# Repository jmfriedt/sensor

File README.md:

Source code for a wireless acoustic sensor short range RADAR reader I used to develop. 15 years of time wasted
on a useless application ... just in case someone can figure out how to make good use of it. Good luck.
If interested enough feel free to reach me, email address easily found on the internet, blueprint for PCBs and prototypes still available if interested.

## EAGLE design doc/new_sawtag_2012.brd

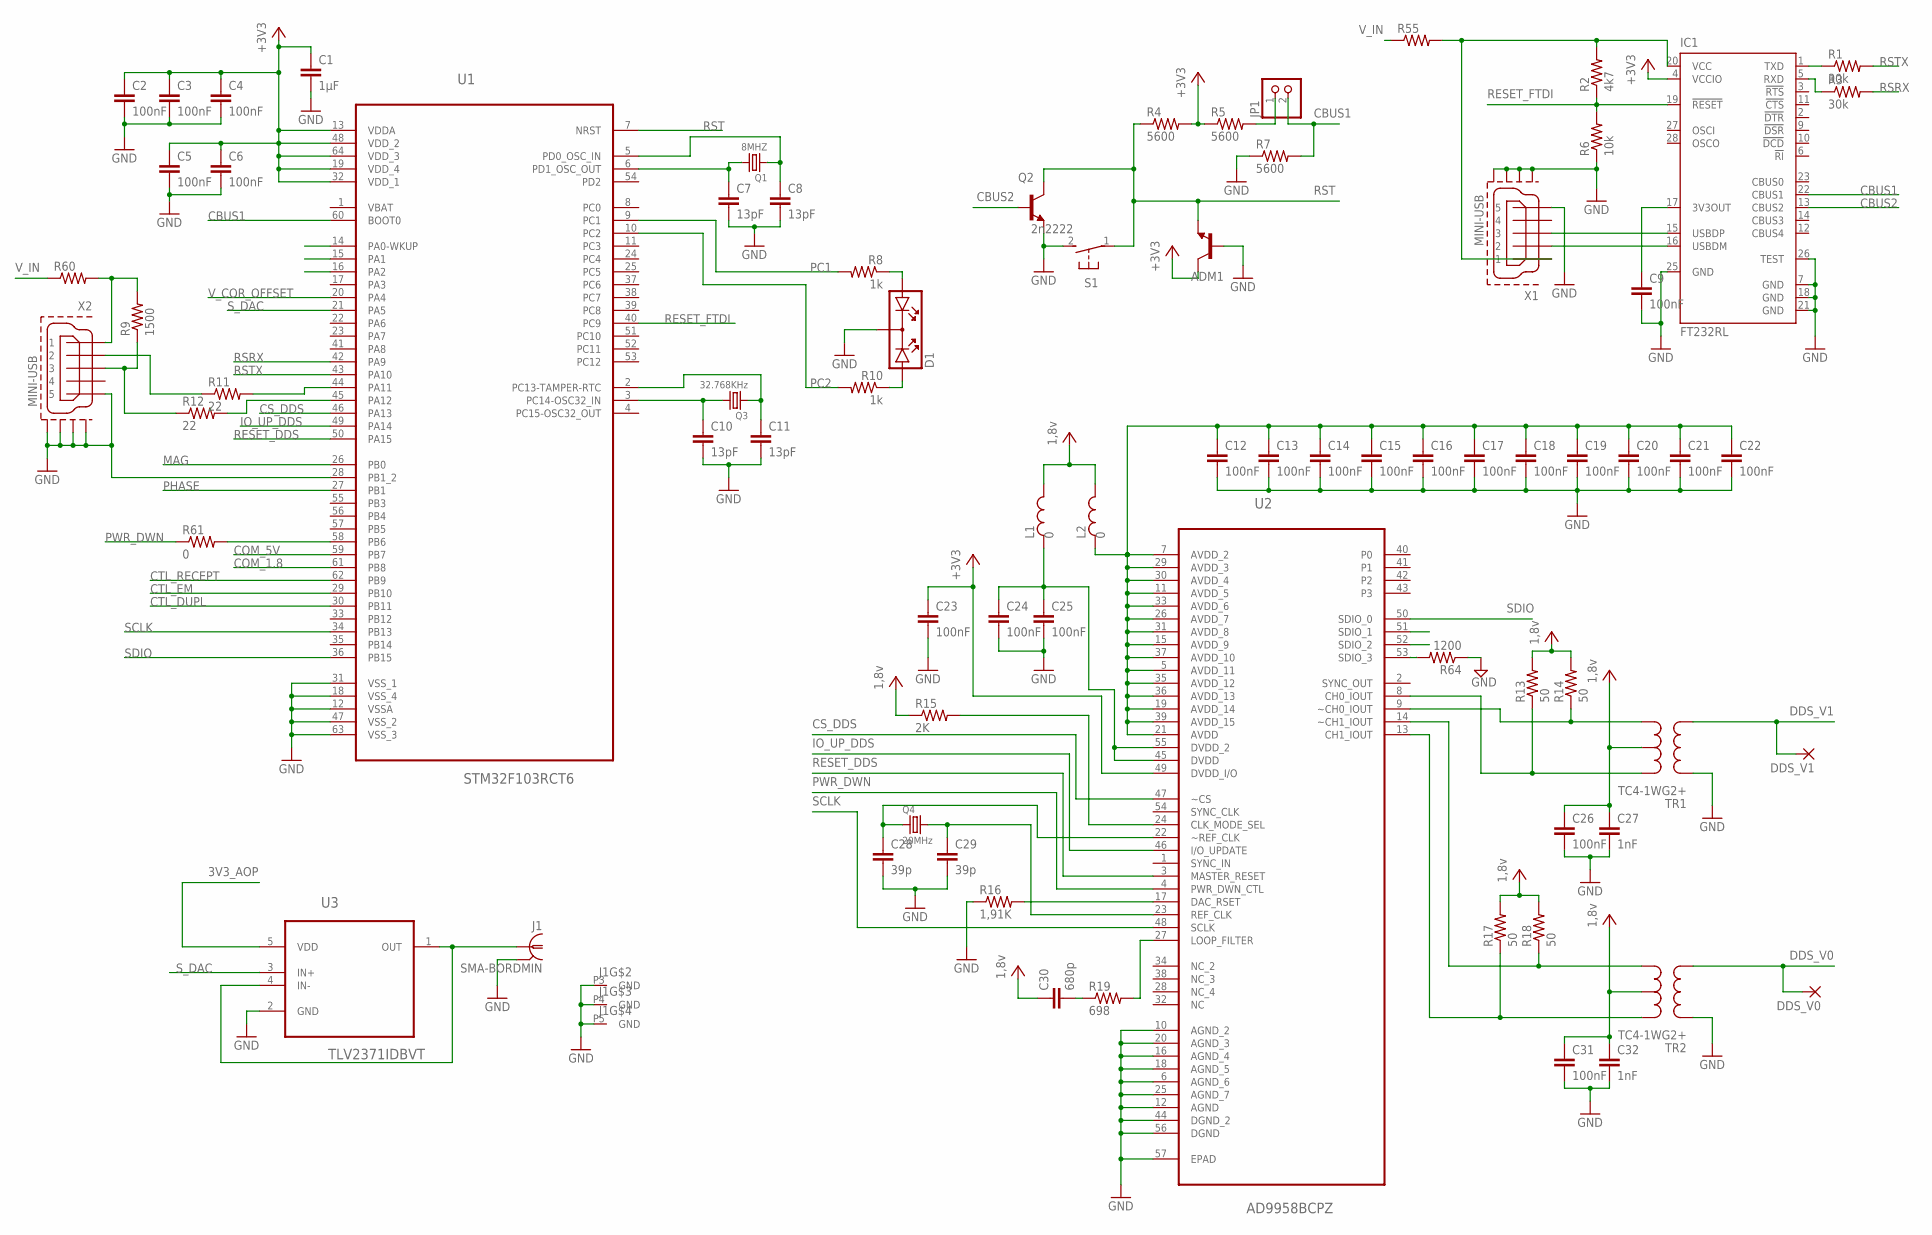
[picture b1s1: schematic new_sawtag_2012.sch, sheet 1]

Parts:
ADM1: TRANSISTOR_NPNSOT23; SOT23
C1: 1µF; C0805
C2, C3, C4, C5, C6, C9, C23, C24, C25, C26, C31: 100nF; C0603
C7, C8, C10, C11: 13pF; C0603
C12, C13, C14, C15, C16, C17, C18, C19, C20, C21, C22: 100nF; C0402
C27, C32: 1nF; C0402
C28, C29: 39p; C0402
C30: 680p; C0402
D1: DUOLED
DDS_V0, DDS_V1: 1,6/0,8
IC1: FT232RL; SSOP28
J1: SMA-BORDMIN; SMA_BORDMIN
JP1: PINHD-1X2; 1X02
L1, L2: 0; 0603
Q1: 8MHZ; SMD_5*3
Q2: 2n2222; SOT23
Q3: 32.768KHz; SMD_32K
Q4: 20MHz; SMD_5*3
R1, R3: 30k; R0402
R2: 4k7; R0402
R4, R5, R7: 5600; R0603
R6: 10k; R0402
R8, R10: 1k; R0603
R9: 1500; R1206
R11, R12: 22; R0603
R13, R14, R17, R18: 50; R0402
R15: 2K; R0402
R16: 1,91K; R0402
R19: 698; R0402
R55, R60: R-US_R2512; R2512
R61: 0; R0603
R64: 1200; R0402
S1: 31-XX; B3F-31XX
TR1, TR2: TC4-1WG2+; AT224-3
U1: STM32F103RCT6; QFP50P1200X1200X160-64N
U2: AD9958BCPZ; QFN50P800X800X100-57N
U3: TLV2371IDBVT; SOT95P280X145-5N
X1, X2: MINI-USB; UX60-MB-5ST

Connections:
3V3_AOP: U3.5 (VDD); also elsewhere on the board
+3V3: ADM1.3 (C), C1.1, C2.1, C3.1, C4.1, C5.1, C6.1, C23.1, IC1.4 (VCCIO), R4.2, R5.1, U1.13 (VDDA), U1.19 (VDD_4), U1.32 (VDD_1), U1.48 (VDD_2), U1.64 (VDD_3), U2.49 (DVDD_I/O); also elsewhere on the board
ALDDS: C12.1, C13.1, C14.1, C15.1, C16.1, C17.1, C18.1, C19.1, C20.1, C21.1, C22.1, L2.1, U2.5 (AVDD_11), U2.7 (AVDD_2), U2.11 (AVDD_5), U2.15 (AVDD_9), U2.19 (AVDD_14), U2.21 (AVDD), U2.26 (AVDD_7), U2.29 (AVDD_3), U2.30 (AVDD_4), U2.31 (AVDD_8), U2.33 (AVDD_6), U2.35 (AVDD_12), U2.36 (AVDD_13), U2.37 (AVDD_10), U2.39 (AVDD_15)
CBUS1: IC1.22 (CBUS1), JP1.2, R7.2, U1.60 (BOOT0)
CBUS2: IC1.13 (CBUS2), Q2.1 (B)
COM_1.8: U1.61 (PB8); also elsewhere on the board
COM_5V: U1.59 (PB7); also elsewhere on the board
CS_DDS: U1.46 (PA13), U2.47 (~CS)
CTL_DUPL: U1.30 (PB11); also elsewhere on the board
CTL_EM: U1.29 (PB10); also elsewhere on the board
CTL_RECEPT: U1.62 (PB9); also elsewhere on the board
DDS_V0: DDS_V0.1, TR2.P6 (P2); also elsewhere on the board
DDS_V1: DDS_V1.1, TR1.P6 (P2); also elsewhere on the board
GND: ADM1.1 (B), C1.2, C2.2, C3.2, C4.2, C5.2, C6.2, C7.2, C8.2, C9.2, C10.2, C11.2, C12.2, C13.2, C14.2, C15.2, C16.2, C17.2, C18.2, C19.2, C20.2, C21.2, C22.2, C23.2, C24.2, C25.2, C26.2, C27.2, C28.2, C29.2, C31.2, C32.2, D1.K, IC1.7 (GND), IC1.18 (GND), IC1.21 (GND), IC1.25 (GND), IC1.26 (TEST), J1.P1 (GND), J1.P3 (GND), J1.P4 (GND), J1.P5 (GND), Q2.2 (E), R6.1, R7.1, R16.1, R64.1, S1.2 (S), TR1.P4 (P1), TR2.P4 (P1), U1.12 (VSSA), U1.18 (VSS_4), U1.28 (PB1_2), U1.31 (VSS_1), U1.47 (VSS_2), U1.63 (VSS_3), U2.6 (AGND_6), U2.10 (AGND_2), U2.12 (AGND), U2.16 (AGND_4), U2.18 (AGND_5), U2.20 (AGND_3), U2.25 (AGND_7), U2.44 (DGND_2), U2.56 (DGND), U2.57 (EPAD), U3.2 (GND), X1.5, X1.M1 (GND1), X1.M2 (GND2), X1.M3 (GND3), X1.M4 (GND4), X2.5, X2.M1 (GND1), X2.M2 (GND2), X2.M3 (GND3), X2.M4 (GND4); also elsewhere on the board
IO_UP_DDS: U1.49 (PA14), U2.46 (I/O_UPDATE)
MAG: U1.26 (PB0); also elsewhere on the board
unnamed: R16.2, U2.17 (DAC_RSET)
unnamed: R19.2, U2.27 (LOOP_FILTER)
unnamed: C30.2, R19.1
unnamed: C28.1, Q4.P$1 (1), U2.22 (~REF_CLK)
unnamed: C29.1, Q4.P$3 (2), U2.23 (REF_CLK)
unnamed: R15.2, U2.24 (CLK_MODE_SEL)
unnamed: R17.1, TR2.P3 (S1), U2.13 (CH1_IOUT)
unnamed: R18.1, TR2.P1 (S3), U2.14 (~CH1_IOUT)
unnamed: R14.1, TR1.P1 (S3), U2.9 (~CH0_IOUT)
unnamed: R13.1, TR1.P3 (S1), U2.8 (CH0_IOUT)
unnamed: C24.1, C25.1, L1.1, U2.45 (DVDD), U2.55 (DVDD_2)
unnamed: R9.2, R60.2, X2.1
unnamed: J1.P2 (1), U3.1 (OUT), U3.4 (IN-)
unnamed: R61.2, U1.58 (PB6)
unnamed: R11.2, U1.44 (PA11)
unnamed: IC1.16 (USBDM), X1.2
unnamed: IC1.20 (VCC), R2.2, R55.2, X1.1
unnamed: R12.2, U1.45 (PA12)
unnamed: IC1.15 (USBDP), X1.3
unnamed: C9.1, IC1.17 (3V3OUT)
unnamed: IC1.1 (TXD), R1.1
unnamed: IC1.5 (RXD), R3.1
unnamed: C8.1, Q1.P$1 (1), U1.5 (PD0_OSC_IN)
unnamed: JP1.1, R5.2
unnamed: C7.1, Q1.P$3 (2), U1.6 (PD1_OSC_OUT)
unnamed: R11.1, X2.2
unnamed: D1.A2, R8.1
unnamed: C10.1, Q3.P$2 (2), U1.3 (PC14-OSC32_IN)
unnamed: C11.1, Q3.P$1 (1), U1.2 (PC13-TAMPER-RTC)
unnamed: D1.A1, R10.1
unnamed: R9.1, R12.1, X2.3
PA7: U1.23 (PA7)
PC1: R8.2, U1.9 (PC1)
PC2: R10.2, U1.10 (PC2)
PHASE: U1.27 (PB1); also elsewhere on the board
PWR_DWN: R61.1, U2.4 (PWR_DWN_CTL)
RESET_DDS: U1.50 (PA15), U2.3 (MASTER_RESET)
RESET_FTDI: IC1.19 (!RESET), R2.1, R6.2, U1.40 (PC9)
RSRX: R3.2, U1.42 (PA9)
RST: ADM1.2 (E), Q2.3 (C), R4.1, S1.1, U1.7 (NRST)
RSTX: R1.2, U1.43 (PA10)
SCLK: U1.34 (PB13), U2.48 (SCLK)
SDIO: U1.36 (PB15), U2.50 (SDIO_0)
SDIO_1: U1.14 (PA0-WKUP), U2.51 (SDIO_1)
SDIO_2: U1.15 (PA1), U2.52 (SDIO_2)
SDIO_3: R64.2, U1.16 (PA2), U2.53 (SDIO_3)
S_DAC: U1.21 (PA5), U3.3 (IN+)
VCC: C26.1, C27.1, C30.1, C31.1, C32.1, L1.2, L2.2, R13.2, R14.2, R15.1, R17.2, R18.2, TR1.P2 (S2), TR2.P2 (S2); also elsewhere on the board
V_COR_OFFSET: U1.20 (PA4); also elsewhere on the board
V_IN: R55.1, R60.1; also elsewhere on the board

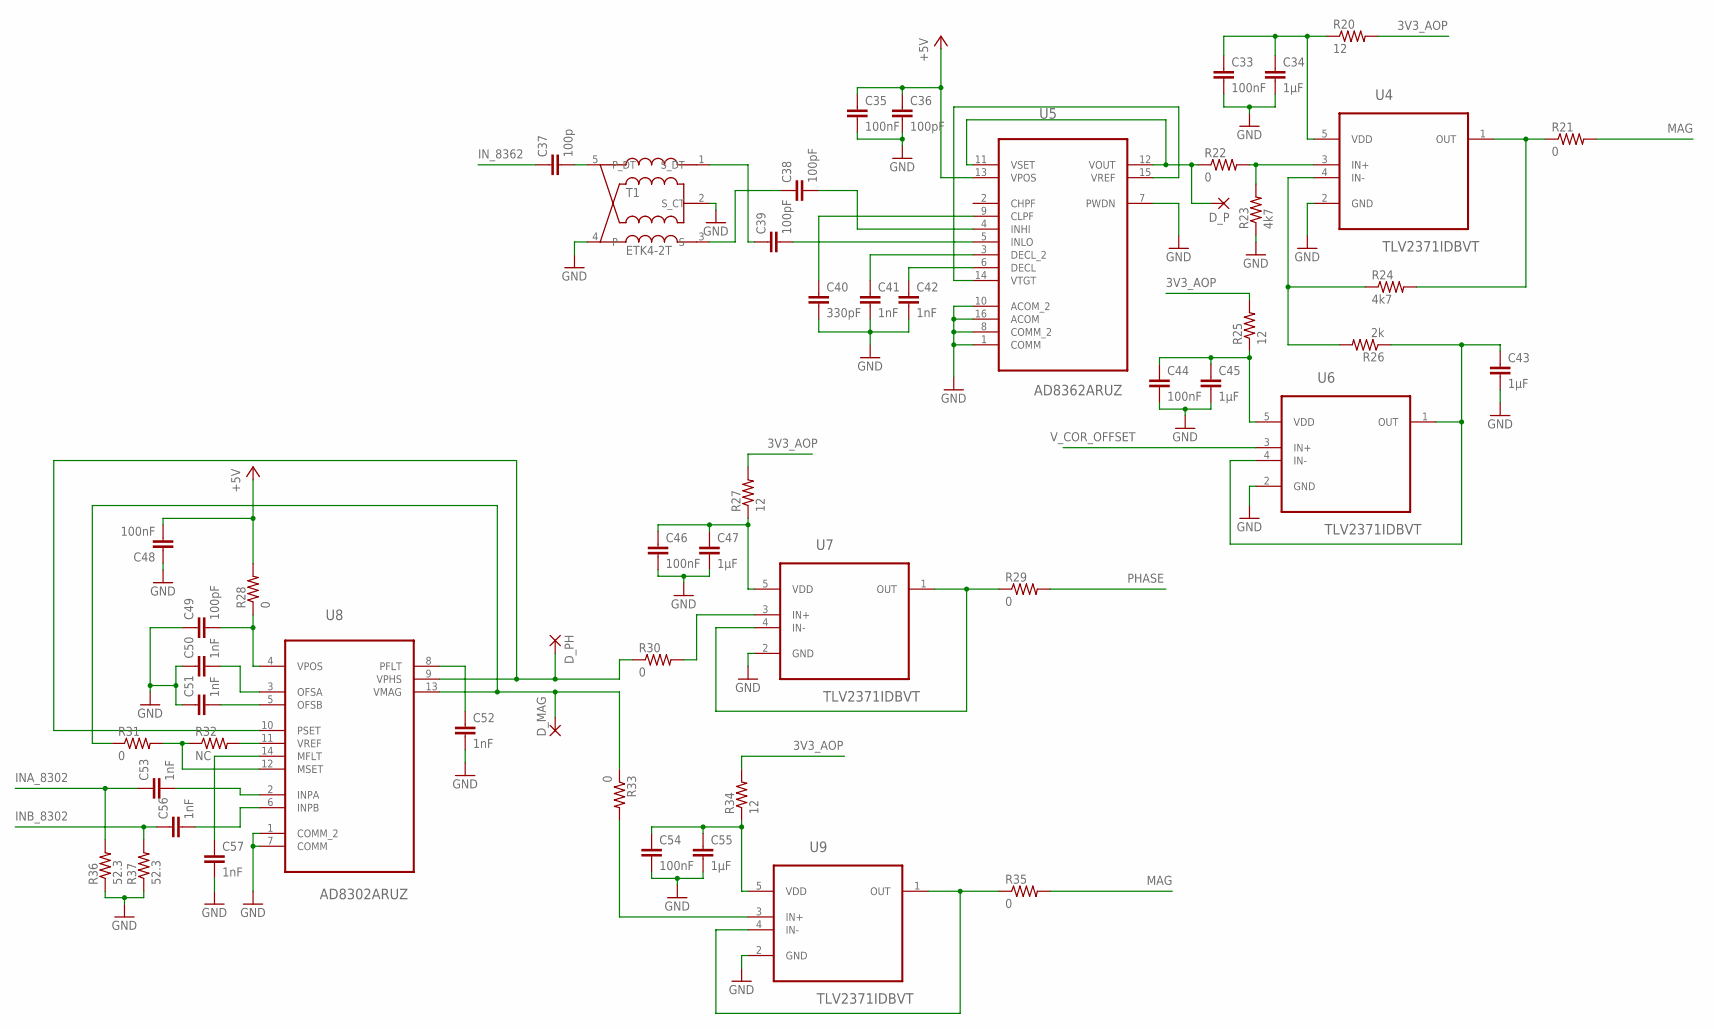
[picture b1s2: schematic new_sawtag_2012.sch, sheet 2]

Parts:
C33, C44, C46, C54: 100nF; C0402
C34, C43, C45, C47, C55: 1µF; C0603
C35, C48: 100nF; C0603
C36: 100pF; C0603
C37: 100p; C0402
C38, C39, C49: 100pF; C0402
C40: 330pF; C0603
C41, C42: 1nF; C0603
C50, C51, C52, C53, C56, C57: 1nF; C0402
D_MAG: 1,6/0,8
D_P: 1,6/0,8
D_PH: 1,6/0,8
R20, R25, R27, R34: 12; R0603
R21, R22, R28, R29, R30, R31, R33, R35: 0; R0603
R23, R24: 4k7; R0603
R26: 2k; R0603
R32: NC; R0603
R36, R37: 52.3; R0603
T1: ETK4-2T; SM-22
U4: TLV2371IDBVT; SOT95P280X145-5N
U5: AD8362ARUZ; SOP65P640X120-16N
U6, U7, U9: TLV2371IDBVT; SOT95P280X145-5N; MPN TLV2371IDBVT
U8: AD8302ARUZ; SOP65P640X120-14N

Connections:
3V3_AOP: R20.2, R25.2, R27.2, R34.2; also elsewhere on the board
+5V: C35.1, C36.1, C48.2, R28.2, U5.13 (VPOS); also elsewhere on the board
GND: C33.2, C34.2, C35.2, C36.2, C40.2, C41.2, C42.2, C43.2, C44.2, C45.2, C46.2, C47.2, C48.1, C49.1, C50.1, C51.1, C52.2, C54.2, C55.2, C57.2, R23.1, R36.1, R37.1, T1.2 (S_CT), T1.4, U4.2 (GND), U5.1 (COMM), U5.7 (PWDN), U5.8 (COMM_2), U5.10 (ACOM_2), U5.16 (ACOM), U6.2 (GND), U7.2 (GND), U8.1 (COMM_2), U8.7 (COMM), U9.2 (GND); also elsewhere on the board
INA_8302: C53.1, R36.2; also elsewhere on the board
INB_8302: C56.1, R37.2; also elsewhere on the board
IN_8362: C37.1; also elsewhere on the board
MAG: R21.2, R35.2; also elsewhere on the board
unnamed: D_P.1, R22.1, U5.11 (VSET), U5.12 (VOUT)
unnamed: R22.2, R23.2, U4.3 (IN+)
unnamed: C42.1, U5.6 (DECL)
unnamed: C41.1, U5.3 (DECL_2)
unnamed: C40.1, U5.9 (CLPF)
unnamed: C39.2, U5.5 (INLO)
unnamed: C38.2, U5.4 (INHI)
unnamed: R24.1, R26.2, U4.4 (IN-)
unnamed: U5.14 (VTGT), U5.15 (VREF)
unnamed: C43.1, R26.1, U6.1 (OUT), U6.4 (IN-)
unnamed: C33.1, C34.1, R20.1, U4.5 (VDD)
unnamed: C50.2, U8.3 (OFSA)
unnamed: C51.2, U8.5 (OFSB)
unnamed: C53.2, U8.2 (INPA)
unnamed: C56.2, U8.6 (INPB)
unnamed: C44.1, C45.1, R25.1, U6.5 (VDD)
unnamed: C49.2, R28.1, U8.4 (VPOS)
unnamed: R30.2, U7.3 (IN+)
unnamed: R29.1, U7.1 (OUT), U7.4 (IN-)
unnamed: R33.2, U9.3 (IN+)
unnamed: R35.1, U9.1 (OUT), U9.4 (IN-)
unnamed: C46.1, C47.1, R27.1, U7.5 (VDD)
unnamed: C54.1, C55.1, R34.1, U9.5 (VDD)
unnamed: D_MAG.1, R31.1, R33.1, U8.13 (VMAG)
unnamed: D_PH.1, R30.1, U8.9 (VPHS), U8.10 (PSET)
unnamed: C39.1, T1.1 (S_DT)
unnamed: C38.1, T1.3 (S)
unnamed: C57.1, U8.14 (MFLT)
unnamed: C52.1, U8.8 (PFLT)
unnamed: C37.2, T1.5 (P_DT)
unnamed: R21.1, R24.2, U4.1 (OUT)
unnamed: R31.2, R32.1, U8.12 (MSET)
unnamed: R32.2, U8.11 (VREF)
PHASE: R29.2; also elsewhere on the board
V_COR_OFFSET: U6.3 (IN+); also elsewhere on the board

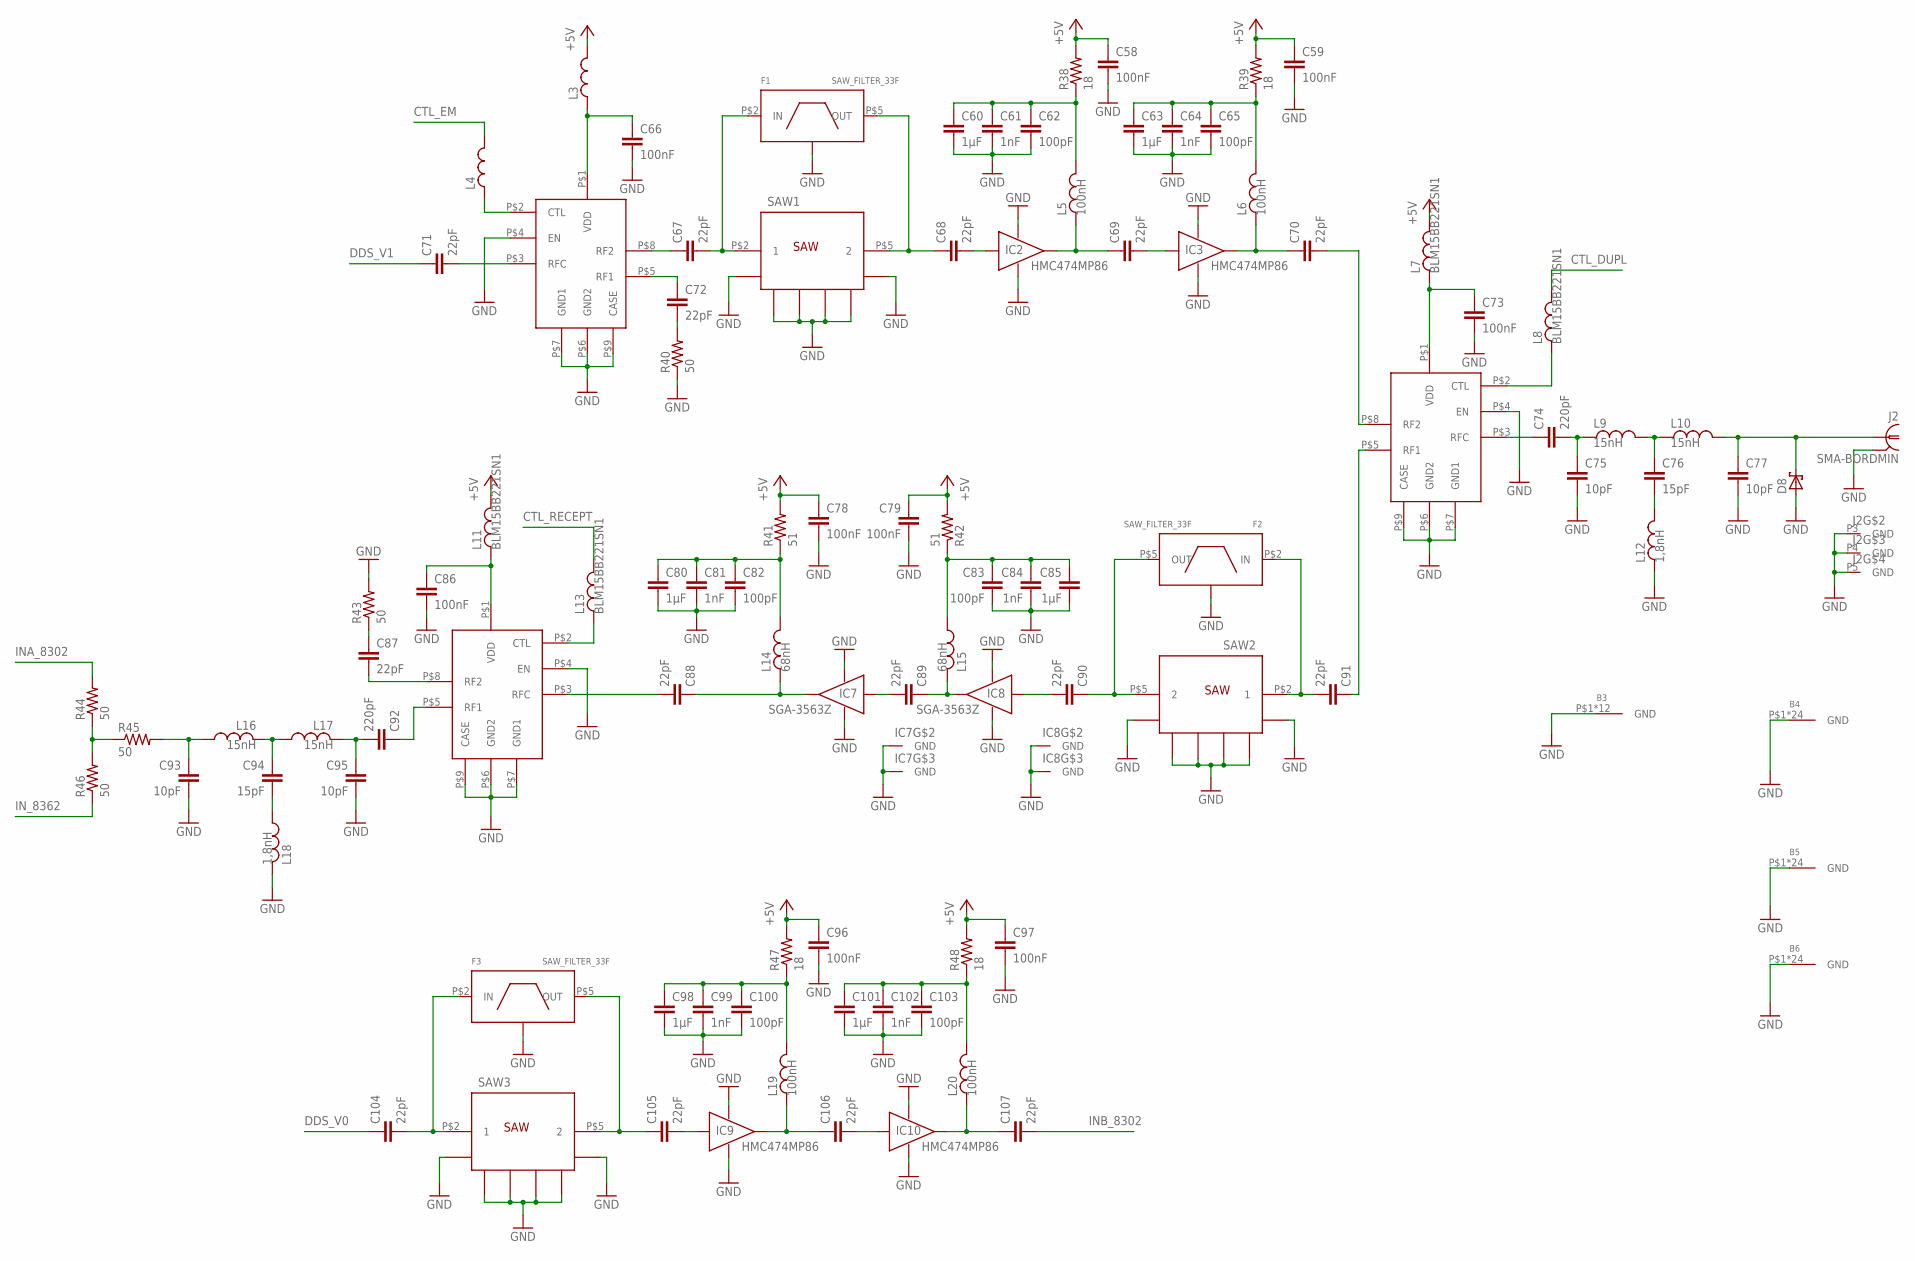
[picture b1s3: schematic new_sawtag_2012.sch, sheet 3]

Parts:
B3: BMIS-102
B4, B5, B6: BMIS-205
C58, C59, C66, C78, C79, C86, C96, C97: 100nF; C0603
C60, C63, C80, C85, C98, C101: 1µF; C0603
C61, C64, C81, C84, C99, C102: 1nF; C0402
C62, C65, C82, C83, C100, C103: 100pF; C0402
C67, C68, C69, C70, C71, C72, C87, C88, C89, C90, C91, C104, C105, C106, C107: 22pF; C0402
C73: 100nF; C0402
C74, C92: 220pF; C0402
C75, C77, C93, C95: 10pF; C0402
C76, C94: 15pF; C0402
D8: SMF5.0AT1; SOD123FL
F1, F2, F3: SAW_FILTER_33F; BOITIER_3-3
IC2, IC3, IC9, IC10: HMC474MP86; VV105
IC4, IC5, IC6: HMC349MS8G; SMT-MS8G
IC7, IC8: SGA-3563Z; SOT363
J2: SMA-BORDMIN; SMA_BORDMIN
L3, L4: L_0402; 0402
L5, L6, L19, L20: 100nH; 0603
L7, L8, L11, L13: BLM15BB221SN1; 0402
L9, L10, L16, L17: 15nH; 0603
L12, L18: 1,8nH; 0603
L14, L15: 68nH; 0603
R38, R39, R47, R48: 18; R0603
R40: 50; R0603
R41, R42: 51; R0603
R43, R44, R45, R46: 50; R0402
SAW1, SAW2, SAW3: SAW_DBLPORT; BOITIER_5-5

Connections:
+5V: C58.1, C59.1, C78.1, C79.1, C96.1, C97.1, L3.2, L7.2, L11.2, R38.2, R39.2, R41.2, R42.2, R47.2, R48.2; also elsewhere on the board
CTL_DUPL: L8.2; also elsewhere on the board
CTL_EM: L4.2; also elsewhere on the board
CTL_RECEPT: L13.2; also elsewhere on the board
DDS_V0: C104.1; also elsewhere on the board
DDS_V1: C71.1; also elsewhere on the board
GND: B3.P$1, B3.P$2, B3.P$3, B3.P$4, B3.P$5, B3.P$6, B3.P$7, B3.P$8, B3.P$9, B3.P$10, B3.P$11, B3.P$12, B4.P$1, B4.P$2, B4.P$3, B4.P$4, B4.P$5, B4.P$6, B4.P$7, B4.P$8, B4.P$9, B4.P$10, B4.P$11, B4.P$12, B4.P$13, B4.P$14, B4.P$15, B4.P$16, B4.P$17, B4.P$18, B4.P$19, B4.P$20, B4.P$21, B4.P$22, B4.P$23, B4.P$24, B5.P$1, B5.P$2, B5.P$3, B5.P$4, B5.P$5, B5.P$6, B5.P$7, B5.P$8, B5.P$9, B5.P$10, B5.P$11, B5.P$12, B5.P$13, B5.P$14, B5.P$15, B5.P$16, B5.P$17, B5.P$18, B5.P$19, B5.P$20, B5.P$21, B5.P$22, B5.P$23, B5.P$24, B6.P$1, B6.P$2, B6.P$3, B6.P$4, B6.P$5, B6.P$6, B6.P$7, B6.P$8, B6.P$9, B6.P$10, B6.P$11, B6.P$12, B6.P$13, B6.P$14, B6.P$15, B6.P$16, B6.P$17, B6.P$18, B6.P$19, B6.P$20, B6.P$21, B6.P$22, B6.P$23, B6.P$24, C58.2, C59.2, C60.2, C61.2, C62.2, C63.2, C64.2, C65.2, C66.2, C73.2, C75.2, C77.2, C78.2, C79.2, C80.2, C81.2, C82.2, C83.2, C84.2, C85.2, C86.2, C93.2, C95.2, C96.2, C97.2, C98.2, C99.2, C100.2, C101.2, C102.2, C103.2, D8.A, F1.P$1, F1.P$3 (GND), F1.P$4 (GND), F1.P$6 (GND), F2.P$1, F2.P$3 (GND), F2.P$4 (GND), F2.P$6 (GND), F3.P$1, F3.P$3 (GND), F3.P$4 (GND), F3.P$6 (GND), IC2.2 (V_1), IC2.4 (V_2), IC3.2 (V_1), IC3.4 (V_2), IC4.P$4 (EN), IC4.P$6 (GND2), IC4.P$7 (GND1), IC4.P$9 (CASE), IC5.P$4 (EN), IC5.P$6 (GND2), IC5.P$7 (GND1), IC5.P$9 (CASE), IC6.P$4 (EN), IC6.P$6 (GND2), IC6.P$7 (GND1), IC6.P$9 (CASE), IC7.P$1 (V_1), IC7.P$2 (GND), IC7.P$4 (V_2), IC7.P$5 (GND), IC8.P$1 (V_1), IC8.P$2 (GND), IC8.P$4 (V_2), IC8.P$5 (GND), IC9.2 (V_1), IC9.4 (V_2), IC10.2 (V_1), IC10.4 (V_2), J2.P1 (GND), J2.P3 (GND), J2.P4 (GND), J2.P5 (GND), L12.1, L18.1, R40.1, R43.2, SAW1.P$1 (GND1), SAW1.P$3 (GND2), SAW1.P$4 (GND3), SAW1.P$6 (GND4), SAW1.P$7 (GND5), SAW1.P$8 (GND6), SAW2.P$1 (GND1), SAW2.P$3 (GND2), SAW2.P$4 (GND3), SAW2.P$6 (GND4), SAW2.P$7 (GND5), SAW2.P$8 (GND6), SAW3.P$1 (GND1), SAW3.P$3 (GND2), SAW3.P$4 (GND3), SAW3.P$6 (GND4), SAW3.P$7 (GND5), SAW3.P$8 (GND6); also elsewhere on the board
INA_8302: R44.2; also elsewhere on the board
INB_8302: C107.2; also elsewhere on the board
IN_8362: R46.1; also elsewhere on the board
unnamed: C67.2, F1.P$2 (IN), SAW1.P$2 (1)
unnamed: C67.1, IC4.P$8 (RF2)
unnamed: C70.1, IC3.3 (OUT), L6.1
unnamed: C68.1, F1.P$5 (OUT), SAW1.P$5 (2)
unnamed: C68.2, IC2.1 (IN)
unnamed: C63.1, C64.1, C65.1, L6.2, R39.1
unnamed: C72.1, IC4.P$5 (RF1)
unnamed: C60.1, C61.1, C62.1, L5.2, R38.1
unnamed: C69.1, IC2.3 (OUT), L5.1
unnamed: C69.2, IC3.1 (IN)
unnamed: C72.2, R40.2
unnamed: C91.2, F2.P$2 (IN), SAW2.P$2 (1)
unnamed: C91.1, IC5.P$5 (RF1)
unnamed: C90.1, F2.P$5 (OUT), SAW2.P$5 (2)
unnamed: C90.2, IC8.P$3 (IN)
unnamed: C89.1, IC8.P$6 (OUT), L15.1
unnamed: C83.1, C84.1, C85.1, L15.2, R42.1
unnamed: C88.1, IC7.P$6 (OUT), L14.1
unnamed: C80.1, C81.1, C82.1, L14.2, R41.1
unnamed: C89.2, IC7.P$3 (IN)
unnamed: C70.2, IC5.P$8 (RF2)
unnamed: C92.1, IC6.P$5 (RF1)
unnamed: C87.2, IC6.P$8 (RF2)
unnamed: C74.1, IC5.P$3 (RFC)
unnamed: C74.2, C75.1, L9.1
unnamed: C76.1, L9.2, L10.1
unnamed: C76.2, L12.2
unnamed: C77.1, D8.C, J2.P2 (1), L10.2
unnamed: C88.2, IC6.P$3 (RFC)
unnamed: C87.1, R43.1
unnamed: C73.1, IC5.P$1 (VDD), L7.1
unnamed: C92.2, C95.1, L17.1
unnamed: C94.1, L16.1, L17.2
unnamed: C94.2, L18.2
unnamed: C93.1, L16.2, R45.2
unnamed: IC5.P$2 (CTL), L8.1
unnamed: C66.1, IC4.P$1 (VDD), L3.1
unnamed: C71.2, IC4.P$3 (RFC)
unnamed: C86.1, IC6.P$1 (VDD), L11.1
unnamed: IC4.P$2 (CTL), L4.1
unnamed: IC6.P$2 (CTL), L13.1
unnamed: R44.1, R45.1, R46.2
unnamed: C104.2, F3.P$2 (IN), SAW3.P$2 (1)
unnamed: C105.1, F3.P$5 (OUT), SAW3.P$5 (2)
unnamed: C105.2, IC9.1 (IN)
unnamed: C98.1, C99.1, C100.1, L19.2, R47.1
unnamed: C106.1, IC9.3 (OUT), L19.1
unnamed: C106.2, IC10.1 (IN)
unnamed: C107.1, IC10.3 (OUT), L20.1
unnamed: C101.1, C102.1, C103.1, L20.2, R48.1

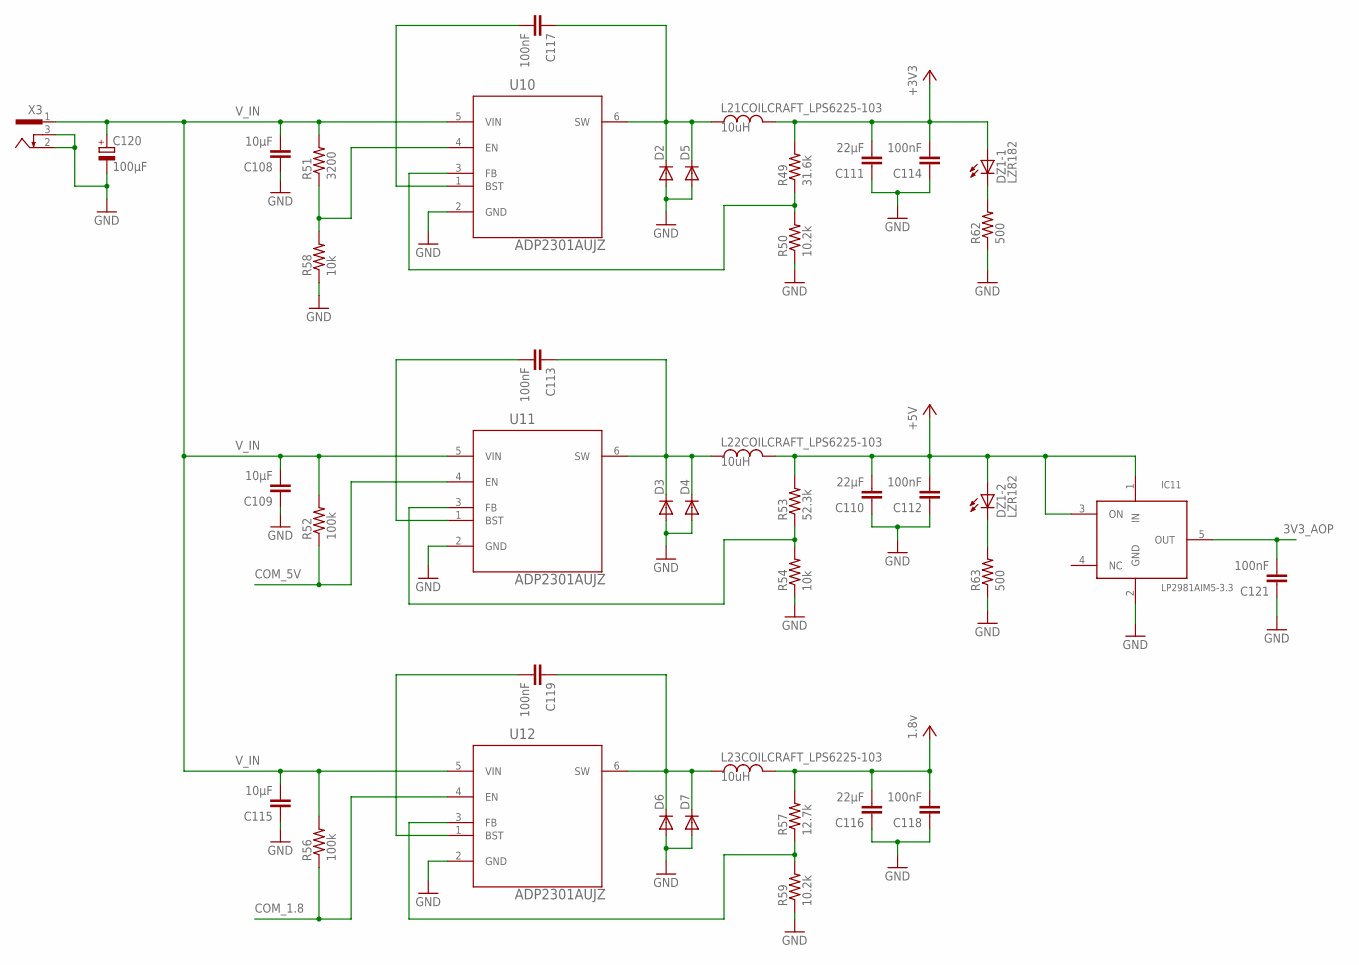
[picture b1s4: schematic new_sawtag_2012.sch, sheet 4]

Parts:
C108, C109, C115: 10µF; C0805
C110, C111, C116: 22µF; C0805
C112, C113, C114, C117, C118, C121: 100nF; C0805
C119: 100nF; C0603
C120: 100µF; 140CLH-1010
D2, D3, D6: DIODE-SMB; SMB
D4, D5, D7: DIODE-SMC; SMC
DZ1: LZR182
IC11: LP2981AIM5-3.3; SOT23-M5
L21COILCRAFT_LPS6225-103, L22COILCRAFT_LPS6225-103, L23COILCRAFT_LPS6225-103: 10uH; L_DCDC_6*6
R49: 31.6k; R0603
R50, R59: 10.2k; R0603
R51: 3200; R0603
R52, R56: 100k; R0603
R53: 52.3k; R0603
R54, R58: 10k; R0603
R57: 12.7k; R0603
R62, R63: 500; R0402
U10, U11, U12: ADP2301AUJZ; SOT95P280X90-6N
X3: 733980-62

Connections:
3V3_AOP: C121.2, IC11.5 (OUT); also elsewhere on the board
+3V3: C111.2, C114.2, DZ1.A1 (A), L21COILCRAFT_LPS6225-103.P$2 (2), R49.2; also elsewhere on the board
+5V: C110.2, C112.2, DZ1.A2 (A), IC11.1 (IN), IC11.3 (ON), L22COILCRAFT_LPS6225-103.P$2 (2), R53.2; also elsewhere on the board
COM_1.8: R56.1, U12.4 (EN); also elsewhere on the board
COM_5V: R52.1, U11.4 (EN); also elsewhere on the board
GND: C108.1, C109.1, C110.1, C111.1, C112.1, C114.1, C115.1, C116.1, C118.1, C120.-, C121.1, D2.A, D3.A, D4.A, D5.A, D6.A, D7.A, IC11.2 (GND), R50.1, R54.1, R58.1, R59.1, R62.1, R63.1, U10.2 (GND), U11.2 (GND), U12.2 (GND), X3.2, X3.3; also elsewhere on the board
unnamed: C113.1, D3.C, D4.C, L22COILCRAFT_LPS6225-103.P$1 (1), U11.6 (SW)
unnamed: C117.1, D2.C, D5.C, L21COILCRAFT_LPS6225-103.P$1 (1), U10.6 (SW)
unnamed: R49.1, R50.2, U10.3 (FB)
unnamed: R53.1, R54.2, U11.3 (FB)
unnamed: C117.2, U10.1 (BST)
unnamed: DZ1.K1 (C), R62.2
unnamed: R51.1, R58.2, U10.4 (EN)
unnamed: C113.2, U11.1 (BST)
unnamed: C119.1, D6.C, D7.C, L23COILCRAFT_LPS6225-103.P$1 (1), U12.6 (SW)
unnamed: R57.1, R59.2, U12.3 (FB)
unnamed: C119.2, U12.1 (BST)
unnamed: DZ1.K2 (C), R63.2
VCC: C116.2, C118.2, L23COILCRAFT_LPS6225-103.P$2 (2), R57.2; also elsewhere on the board
V_IN: C108.2, C109.2, C115.2, C120.+, R51.2, R52.2, R56.2, U10.5 (VIN), U11.5 (VIN), U12.5 (VIN), X3.1; also elsewhere on the board

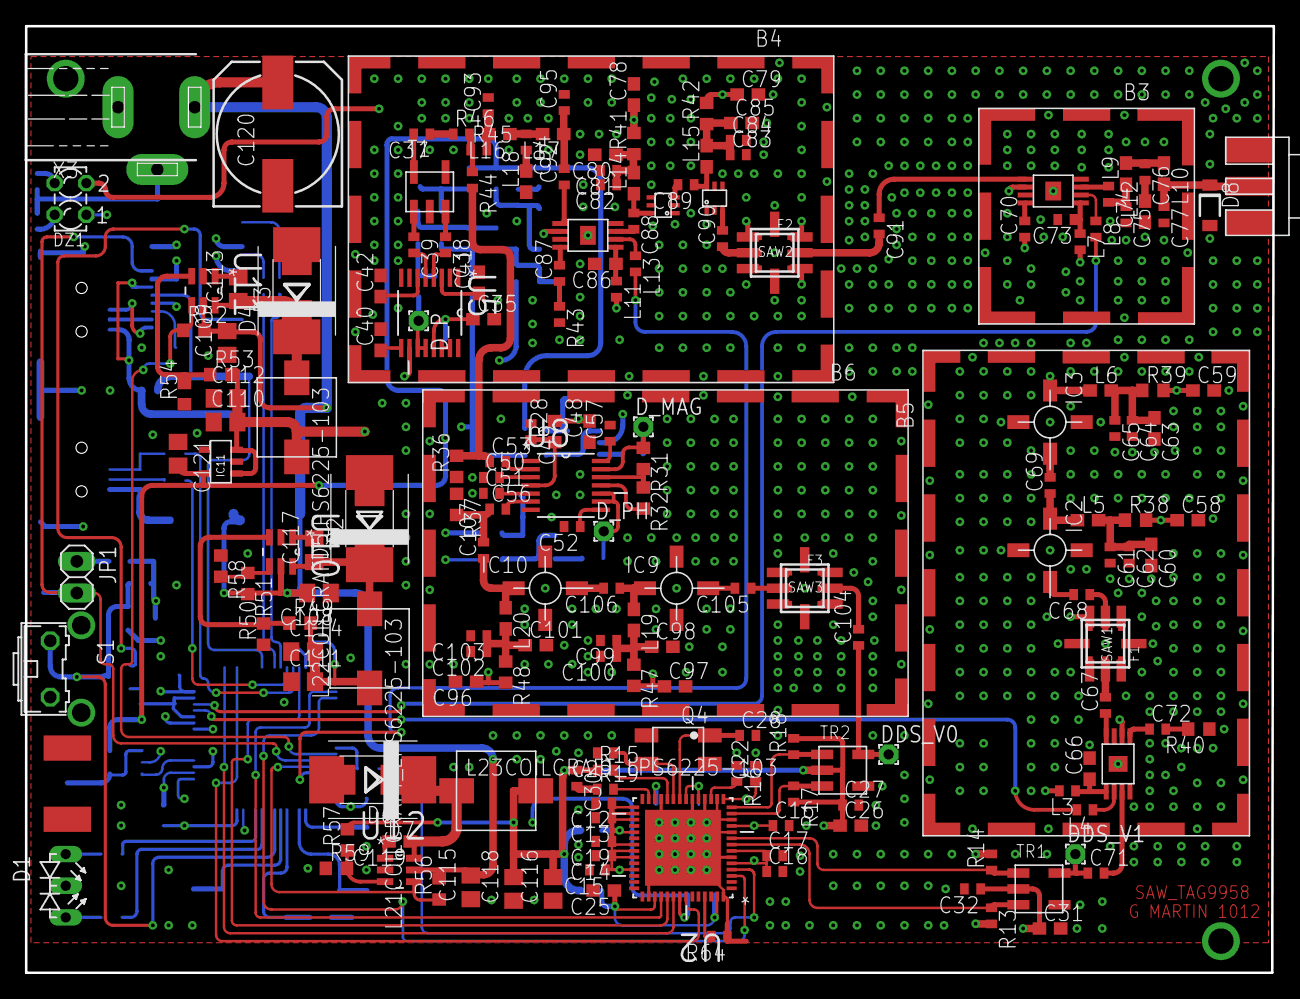
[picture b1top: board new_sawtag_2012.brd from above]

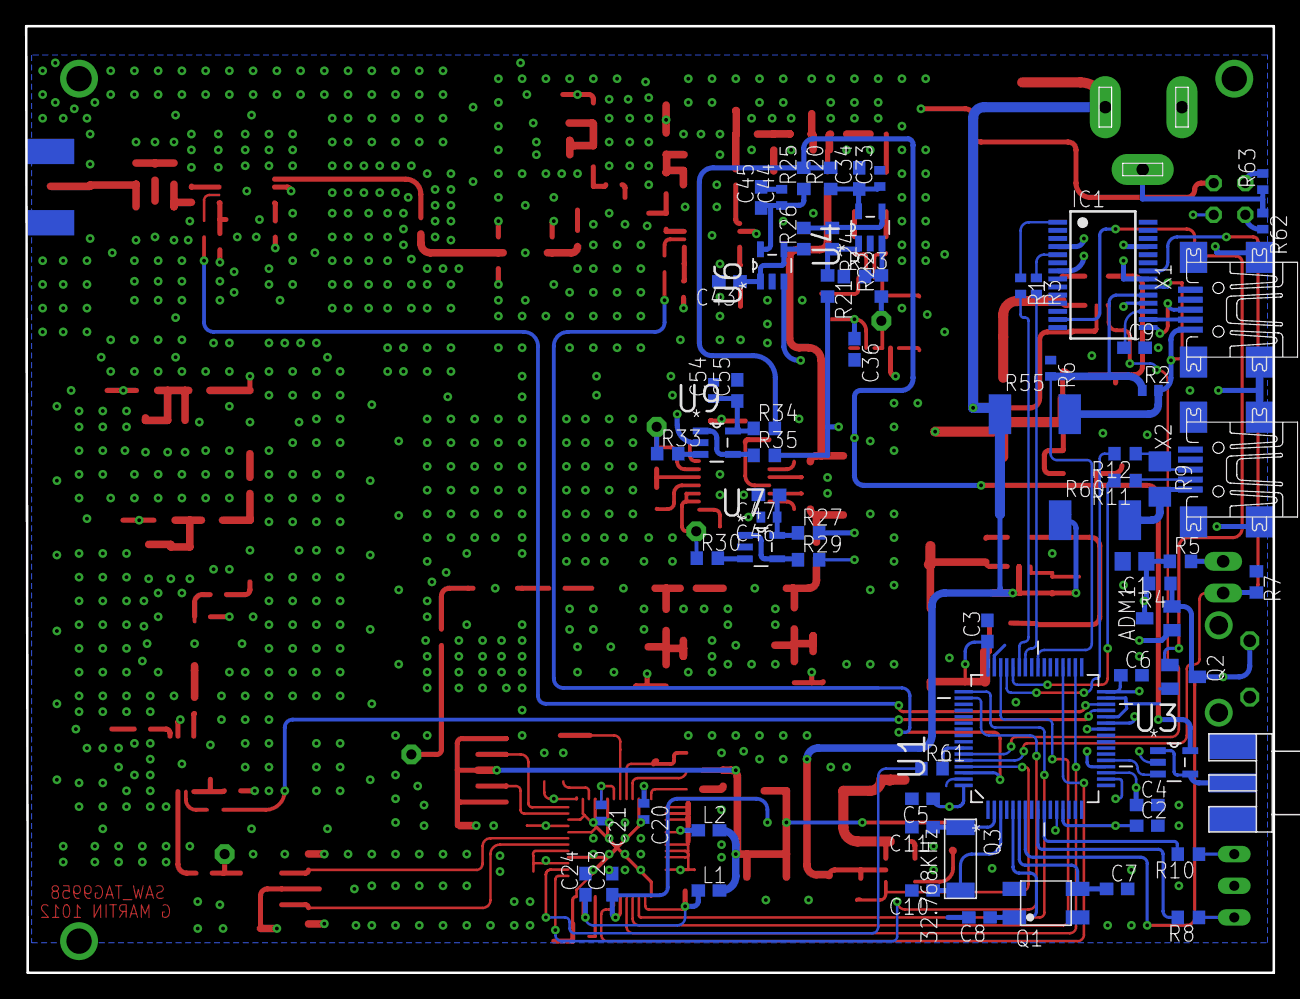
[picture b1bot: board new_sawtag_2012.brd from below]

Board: 4 copper layers, 100.1 x 76.0 mm, 270 parts (71 on the bottom side), 164 nets.

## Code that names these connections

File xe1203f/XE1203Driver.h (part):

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**                                  *  uC     * XE1203    * P.x  **
*******************************************************************/

  #define DCLK         	((_U16)0x0080)       //*  In     *  Out      * PB7
  #define DATA            ((_U16)0x0100)       //*  In     *  Out      * PB8
  #define PATTERN         ((_U16)0x0040)       //*  In     *  Out      * PB6
  #define SYCHRO_OSC         GPIO_Pin_4        //*  Out     *  In      * PB1

/*******************************************************************
** Port 1 pins definitions                                        **
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**                                  *  uC     * XE1203    * 1.x  **
*******************************************************************/

  #define SCK             ((_U16)0x2000)      //*  Out     *  In      * PB13	
  #define SI              ((_U16)0x8000)      //*  Out     *  In      * PB15
  #define SO              ((_U16)0x4000)      //*  In      *  Out     * PB14
  #define EN              ((_U16)0x1000)      //*  Out     *  In      * PB12
  #define TX              ((_U16)0x0400)      //*  Out     *  In      * PB10
  #define RX              ((_U16)0x0200)      //*  Out     *  In      * PB9
  #define DATAIN          ((_U16)0x0020)      //*  Out     *  In      * PB5
  #define SWITCH          ((_U16)0x0800)      //*  Out     *  In      * PB11

/*******************************************************************
** XE1203 definitions                                             **
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
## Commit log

2022-07-17 cleanup
